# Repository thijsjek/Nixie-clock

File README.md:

# Nixie-clock
Raspberry pi zero based nixie tube clock
https://thijskanters.wordpress.com for detailed information and PCB design files

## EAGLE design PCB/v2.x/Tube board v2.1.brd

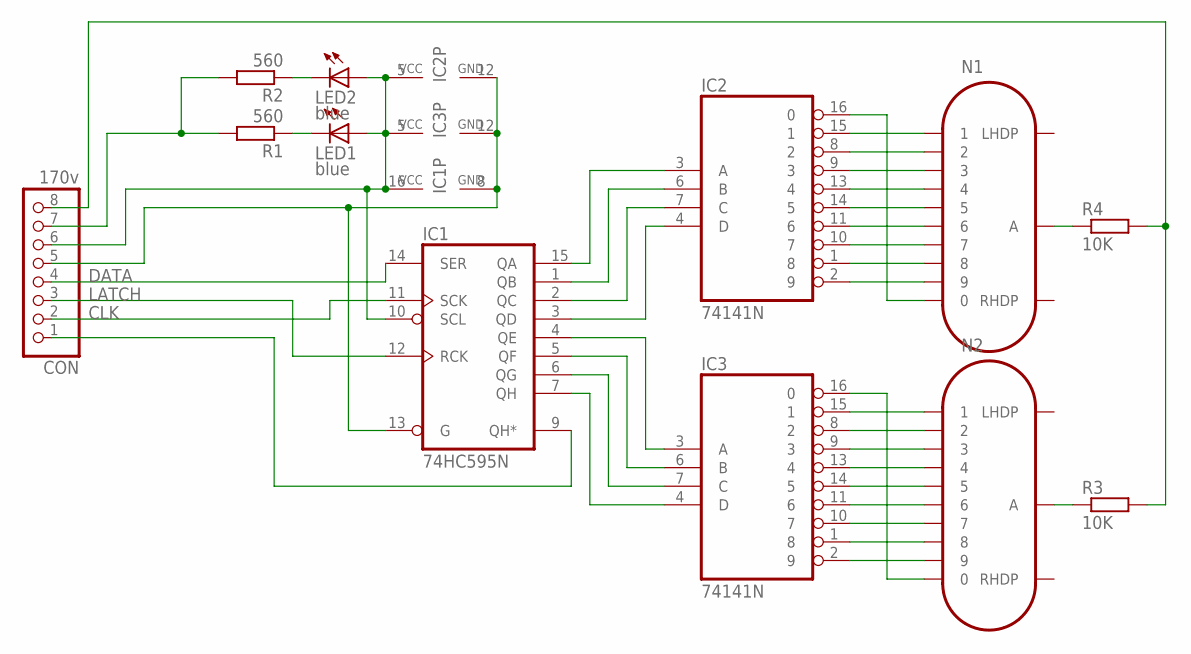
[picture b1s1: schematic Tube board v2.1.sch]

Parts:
CON: 170v; 1X08
IC1: 74HC595N; DIL16
IC2, IC3: 74141N; DIL16
LED1, LED2: blue; LED3MM
N1, N2: IN-14
R1, R2: 560; 0204/7
R3, R4: 10K; 0204/7

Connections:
170V: CON.8, R3.2, R4.2
CLK: CON.2, IC1.11 (SCK)
DATA: CON.4, IC1.14 (SER)
GND: CON.5, IC1.8 (GND), IC1.13 (G), IC2.12 (GND), IC3.12 (GND)
LATCH: CON.3, IC1.12 (RCK)
unnamed: LED1.K (C), R1.1
unnamed: CON.7, R1.2, R2.2
unnamed: LED2.K (C), R2.1
unnamed: IC1.15 (QA), IC2.3 (A)
unnamed: IC1.1 (QB), IC2.6 (B)
unnamed: IC1.2 (QC), IC2.7 (C)
unnamed: IC1.3 (QD), IC2.4 (D)
unnamed: IC1.7 (QH), IC3.4 (D)
unnamed: IC1.6 (QG), IC3.7 (C)
unnamed: IC1.5 (QF), IC3.6 (B)
unnamed: IC1.4 (QE), IC3.3 (A)
unnamed: CON.1, IC1.9 (QH*)
unnamed: IC2.16 (0), N1.0
unnamed: IC2.15 (1), N1.1
unnamed: IC2.8 (2), N1.2
unnamed: IC2.9 (3), N1.3
unnamed: IC2.13 (4), N1.4
unnamed: IC2.14 (5), N1.5
unnamed: IC2.11 (6), N1.6
unnamed: IC2.10 (7), N1.7
unnamed: IC2.1 (8), N1.8
unnamed: IC2.2 (9), N1.9
unnamed: IC3.15 (1), N2.1
unnamed: IC3.8 (2), N2.2
unnamed: IC3.9 (3), N2.3
unnamed: IC3.13 (4), N2.4
unnamed: IC3.14 (5), N2.5
unnamed: IC3.11 (6), N2.6
unnamed: IC3.10 (7), N2.7
unnamed: IC3.1 (8), N2.8
unnamed: IC3.2 (9), N2.9
unnamed: IC3.16 (0), N2.0
unnamed: N2.A, R3.1
unnamed: N1.A, R4.1
VCC: CON.6, IC1.10 (SCL), IC1.16 (VCC), IC2.5 (VCC), IC3.5 (VCC), LED1.A, LED2.A

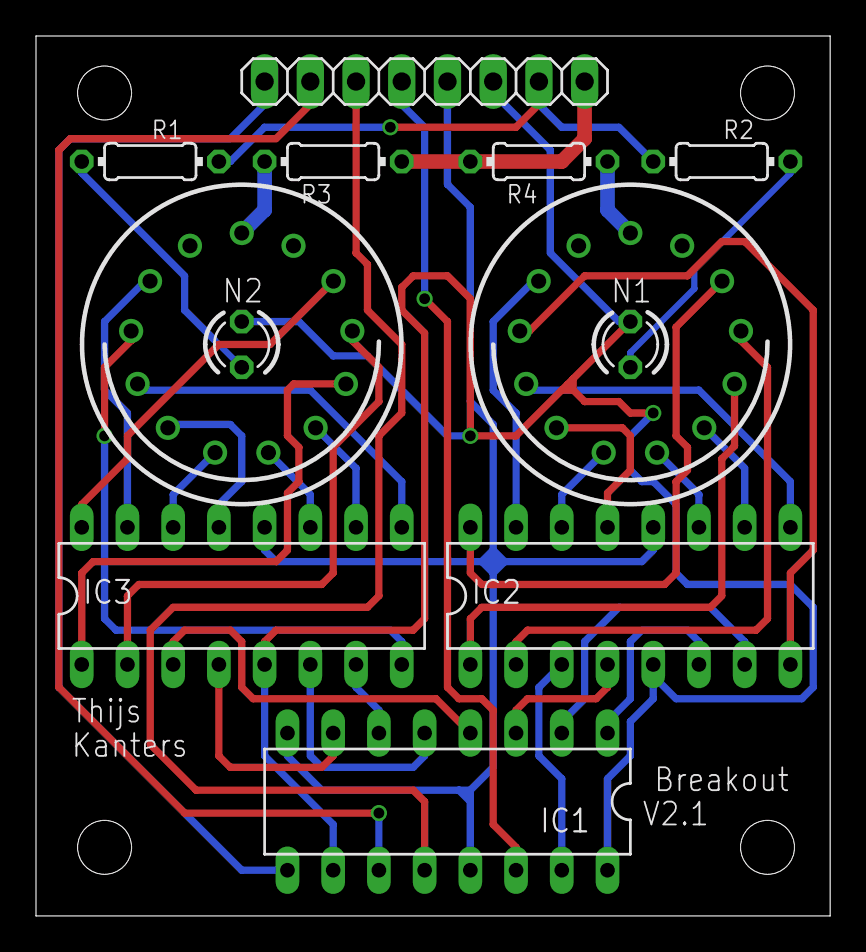
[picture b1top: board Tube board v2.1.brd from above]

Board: 2 copper layers, 44.1 x 48.9 mm, 12 parts (0 on the bottom side), 40 nets.

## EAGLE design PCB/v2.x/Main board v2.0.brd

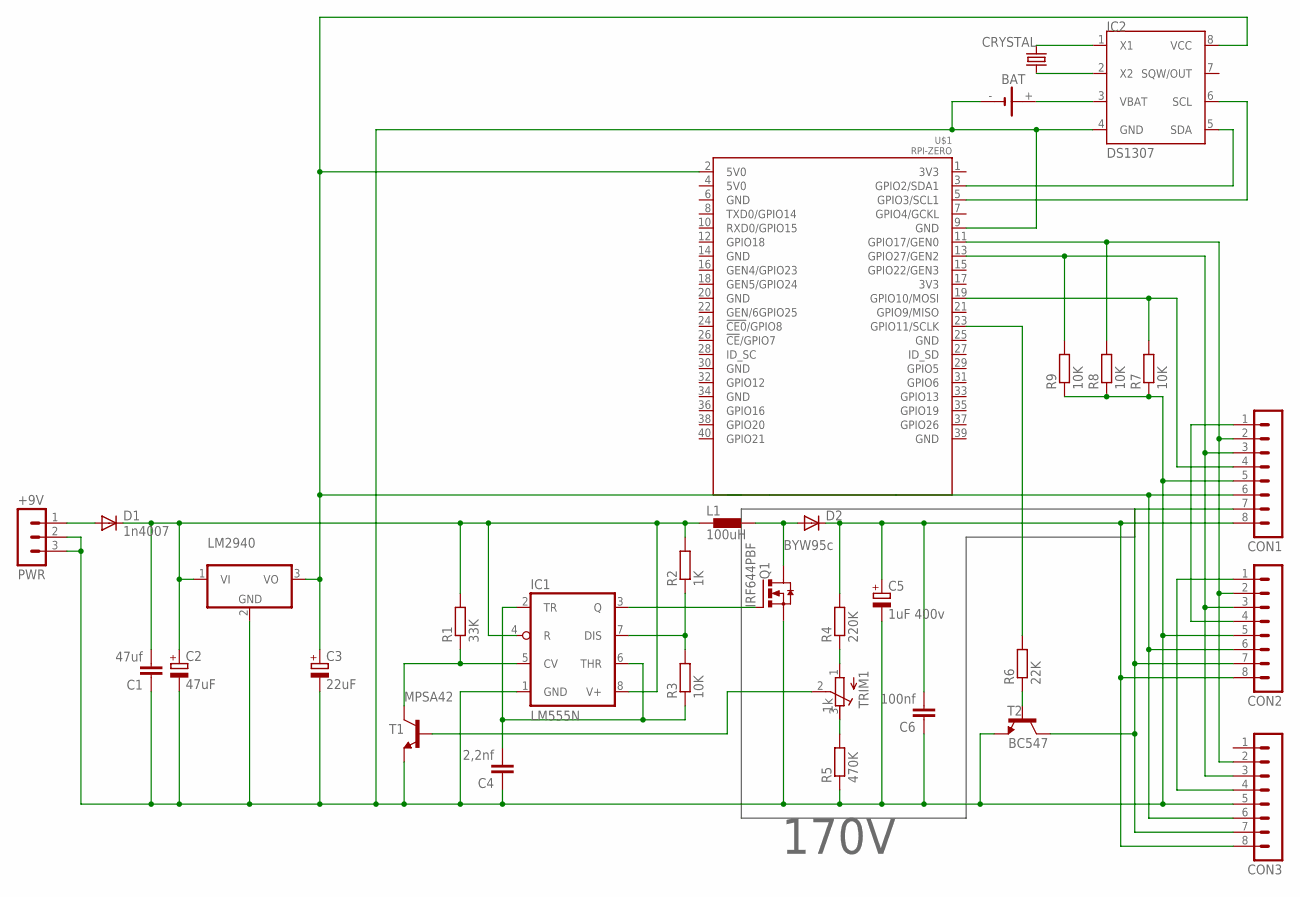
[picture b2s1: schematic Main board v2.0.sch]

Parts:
BAT: CH291-1220LF
C1: 47uf; C025-025X050
C2: 47uF; E5-8,5
C3: 22uF; E2,5-4R
C4: 2,2nf; C5B2.5
C5: 1uF 400v; E2,5-6
C6: 100nf; C075-032X103
CON1, CON2, CON3: MA08-1
CRYSTAL: crystal; TC26H
D1: 1n4007; DO41-10
D2: BYW95c; SOD64-10
IC1: LM555N; DIL08
IC2: DS1307; SOIC-8
L1: 100uH; DR1030
LM2940: 7824T; TO220V
PWR: +9V; MA03-1
Q1: IRF644PBF; TO262-H
R1: 33K; 0207/10
R2: 1K; 0207/10
R3, R7, R8, R9: 10K; 0207/10
R4: 220K; 0207/10
R5: 470K; 0207/10
R6: 22K; 0207/10
T1: MPSA42; TO92-EBC
T2: BC547; TO92-CBE
TRIM1: 1k; RTRIM64W
U$1: RPI-ZERO; RASPBERRYPI_BASTELSTUBE_V13_RASPI_BOARD_B+_FULL

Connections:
5V0: C3.+, CON1.6, CON2.6, CON3.6, IC2.8 (VCC), LM2940.3 (VO), U$1.2 (5V0)
170V: C5.+, C6.2, CON1.8, CON2.8, CON3.8, D2.C, R4.2
CLK: CON1.2, CON2.2, CON3.2, R8.2, U$1.11 (GPIO17/GEN0)
DATA: CON1.4, R7.2, U$1.19 (GPIO10/MOSI)
GND@1: BAT.-, C1.1, C2.-, C3.-, C4.1, C5.-, C6.1, CON1.5, CON2.5, CON3.5, IC1.1 (GND), IC2.4 (GND), LM2940.2 (GND), PWR.2, PWR.3, Q1.3 (S), R5.1, R7.1, R8.1, R9.1, T1.E, T2.E, U$1.9 (GND)
LATCH: CON1.3, CON2.3, CON3.3, R9.2, U$1.13 (GPIO27/GEN2)
LED: CON1.7, CON2.7, CON3.7, T2.C
LEDDRIVER: R6.2, U$1.23 (GPIO11/SCLK)
unnamed: CON1.1, CON2.4
unnamed: CON2.1, CON3.4
unnamed: R4.1, TRIM1.1 (A)
unnamed: R6.1, T2.B
unnamed: IC2.6 (SCL), U$1.5 (GPIO3/SCL1)
unnamed: IC2.5 (SDA), U$1.3 (GPIO2/SDA1)
unnamed: CRYSTAL.1, IC2.2 (X2)
unnamed: CRYSTAL.2, IC2.1 (X1)
unnamed: D1.A, PWR.1
unnamed: IC1.3 (Q), Q1.1 (G)
unnamed: IC1.7 (DIS), R2.1, R3.2
unnamed: IC1.5 (CV), R1.1, T1.C
unnamed: C4.2, IC1.2 (TR), IC1.6 (THR), R3.1
unnamed: D2.A, L1.2, Q1.2 (D)
unnamed: T1.B, TRIM1.2 (S)
unnamed: R5.2, TRIM1.3 (E)
V+: C1.2, C2.+, D1.C, IC1.4 (R), IC1.8 (V+), L1.1, LM2940.1 (VI), R1.2, R2.2
VBAT: BAT.+, IC2.3 (VBAT)

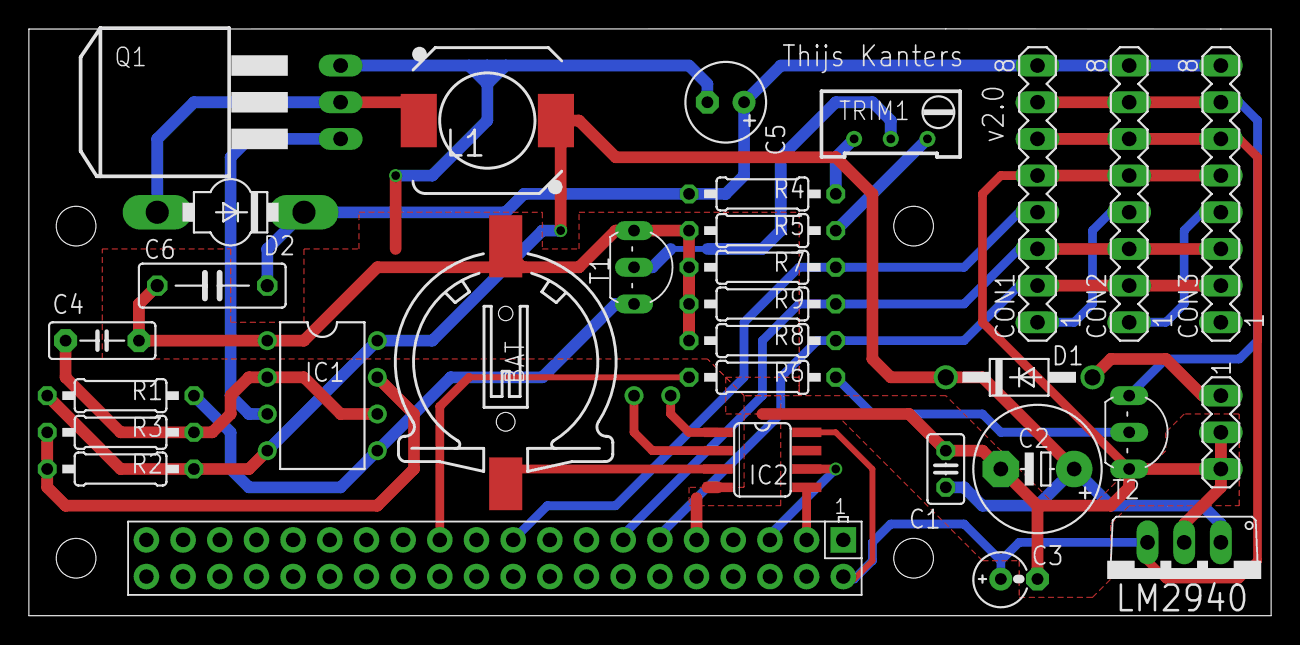
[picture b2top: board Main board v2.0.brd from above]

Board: 2 copper layers, 86.0 x 40.6 mm, 32 parts (1 on the bottom side), 26 nets.

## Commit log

2016-04-08 Added files via upload
2016-04-20 Create test
2016-04-20 Delete led.py
    moved to folder
2016-04-20 Create Rules
2016-04-20 Create 123
2016-04-20 Create 1234
2016-04-20 Create 12345
